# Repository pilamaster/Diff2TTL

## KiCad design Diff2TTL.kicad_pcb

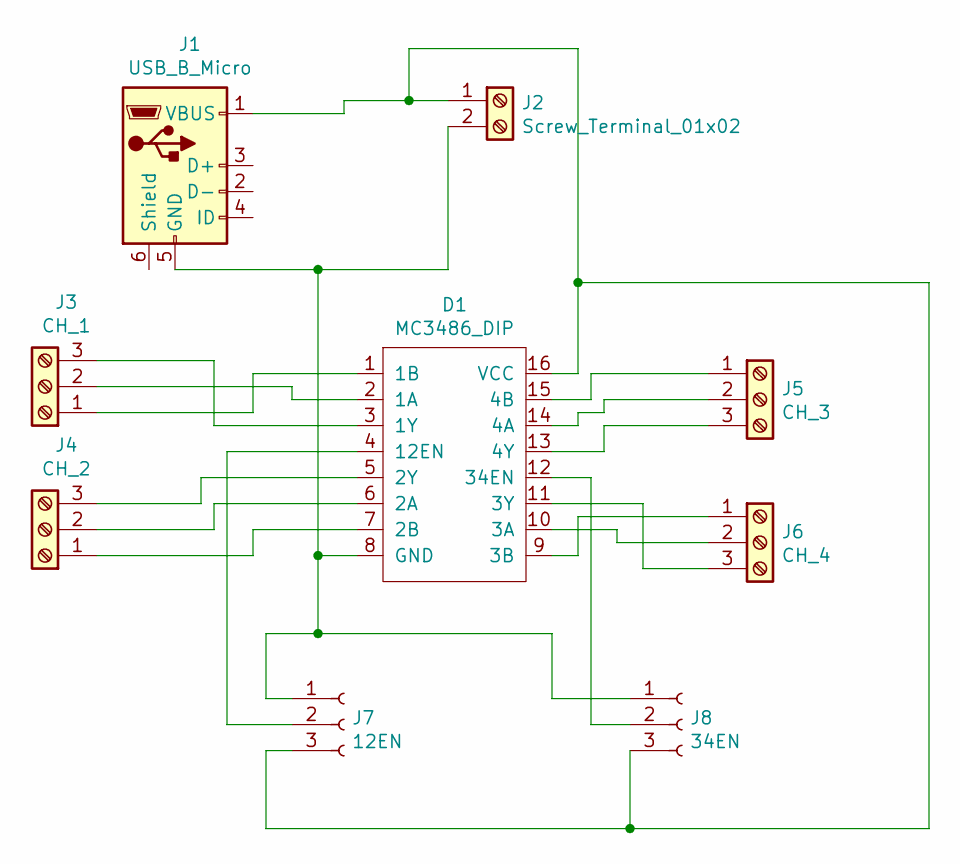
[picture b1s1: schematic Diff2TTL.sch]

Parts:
D1: MC3486_DIP; DIP-16_W7.62mm_LongPads
J1: USB_B_Micro; USB_Micro-B_Molex_47346-0001
J2: Screw_Terminal_01x02; TerminalBlock_bornier-2_P5.08mm
J3: CH_1; TerminalBlock_bornier-3_P5.08mm
J4: CH_2; TerminalBlock_bornier-3_P5.08mm
J5: CH_3; TerminalBlock_bornier-3_P5.08mm
J6: CH_4; TerminalBlock_bornier-3_P5.08mm
J7: 12EN; PinHeader_1x03_P2.54mm_Vertical
J8: 34EN; PinHeader_1x03_P2.54mm_Vertical

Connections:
unnamed: D1.1 (1B), J3.1
unnamed: D1.2 (1A), J3.2
unnamed: D1.3 (1Y), J3.3
unnamed: D1.4 (12EN), J7.2
unnamed: D1.5 (2Y), J4.3
unnamed: D1.6 (2A), J4.2
unnamed: D1.7 (2B), J4.1
unnamed: D1.8 (GND), J1.5 (GND), J2.2, J7.1, J8.1
unnamed: D1.9 (3B), J6.1
unnamed: D1.10 (3A), J6.2
unnamed: D1.11 (3Y), J6.3
unnamed: D1.12 (34EN), J8.2
unnamed: D1.13 (4Y), J5.3
unnamed: D1.14 (4A), J5.2
unnamed: D1.15 (4B), J5.1
unnamed: D1.16 (VCC), J1.1 (VBUS), J2.1, J7.3, J8.3

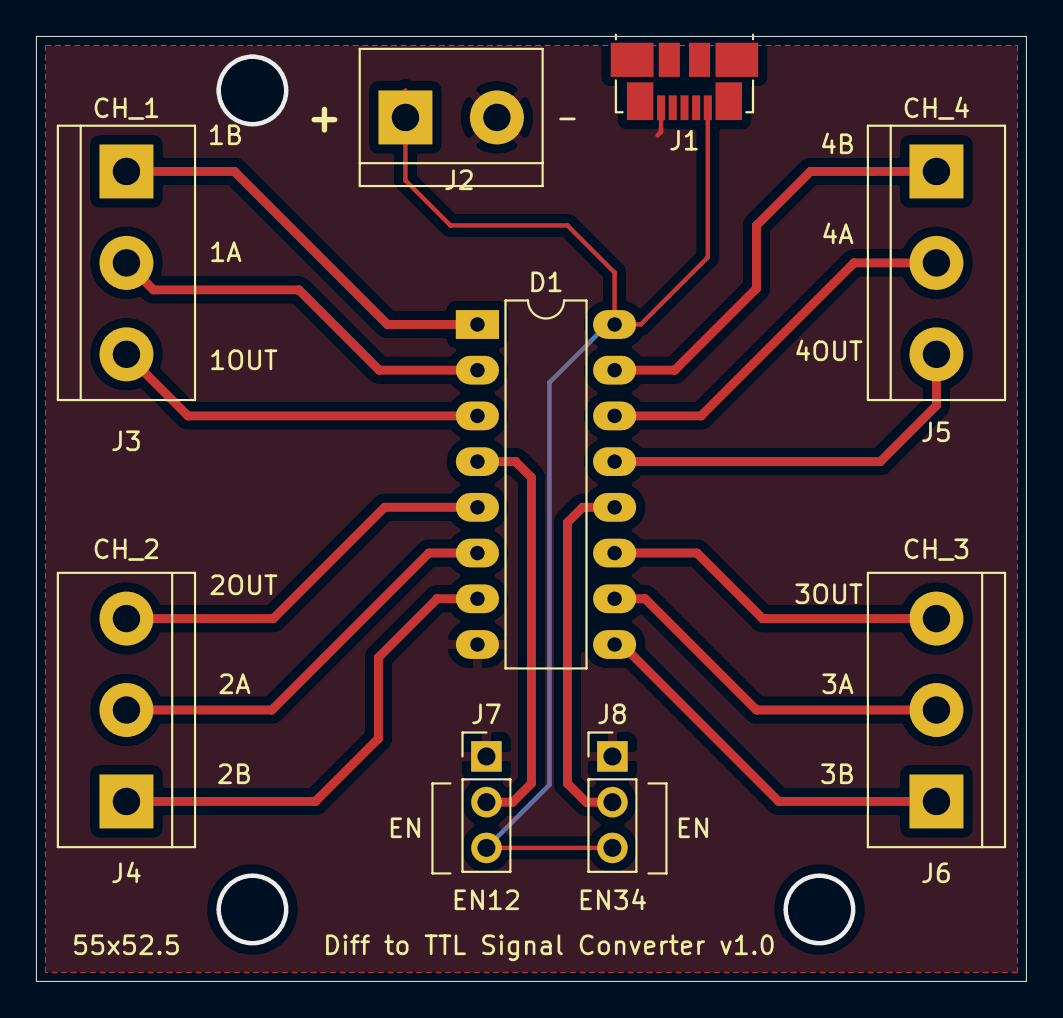
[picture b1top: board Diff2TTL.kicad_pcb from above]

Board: 2 copper layers, 55.0 x 52.5 mm, 9 parts (0 on the bottom side), 16 nets.

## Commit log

2021-10-07 Differential to TTL signal converter
    Differential to TTL signal converter
